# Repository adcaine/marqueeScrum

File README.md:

marqueeScrum
============

This will display a marquee message during scrums to keep people on time

This is strictly a work in progress at this time.

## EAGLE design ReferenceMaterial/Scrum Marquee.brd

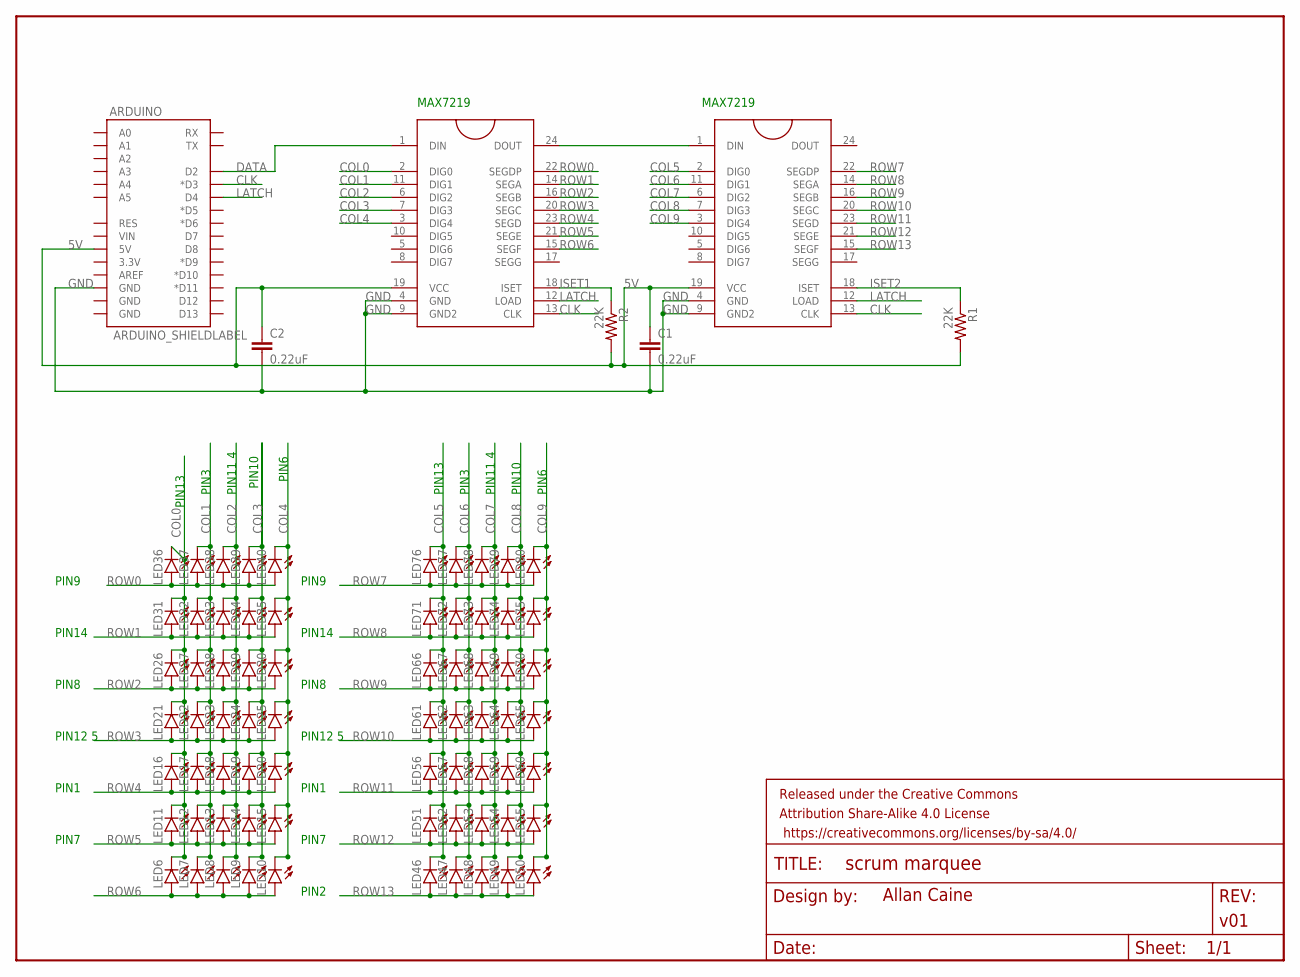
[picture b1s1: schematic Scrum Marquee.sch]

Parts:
ARDUINO: ARDUINO_SHIELDLABEL; DUEMILANOVE_SHIELD
C1, C2: 0.22uF; CAP-PTH-SMALL-KIT
FRAME1: FRAME-LETTER; CREATIVE_COMMONS
LED6, LED7, LED8, LED9, LED10, LED11, LED12, LED13, LED14, LED15, LED16, LED17, LED18, LED19, LED20, LED21, LED22, LED23, LED24, LED25, LED26, LED27, LED28, LED29, LED30, LED31, LED32, LED33, LED34, LED35, LED36, LED37, LED38, LED39, LED40, LED46, LED47, LED48, LED49, LED50, LED51, LED52, LED53, LED54, LED55, LED56, LED57, LED58, LED59, LED60, LED61, LED62, LED63, LED64, LED65, LED66, LED67, LED68, LED69, LED70, LED71, LED72, LED73, LED74, LED75, LED76, LED77, LED78, LED79, LED80: LED5MM
MAX7219DIP: MAX7219DIP; DIL24
R1, R2: 22K; AXIAL-0.4
U$2: MAX7219DIP; DIL24

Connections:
5V: ARDUINO.5V, C1.1, C2.1, MAX7219DIP.19 (VCC), R1.P$2 (2), R2.P$2 (2), U$2.19 (VCC)
CLK: ARDUINO.D3 (*D3), MAX7219DIP.13 (CLK), U$2.13 (CLK)
COL0: LED6.K (C), LED11.K (C), LED16.K (C), LED21.K (C), LED26.K (C), LED31.K (C), LED36.K (C), MAX7219DIP.2 (DIG0)
COL1: LED7.K (C), LED12.K (C), LED17.K (C), LED22.K (C), LED27.K (C), LED32.K (C), LED37.K (C), MAX7219DIP.11 (DIG1)
COL2: LED8.K (C), LED13.K (C), LED18.K (C), LED23.K (C), LED28.K (C), LED33.K (C), LED38.K (C), MAX7219DIP.6 (DIG2)
COL3: LED9.K (C), LED14.K (C), LED19.K (C), LED24.K (C), LED29.K (C), LED34.K (C), LED39.K (C), MAX7219DIP.7 (DIG3)
COL4: LED10.K (C), LED15.K (C), LED20.K (C), LED25.K (C), LED30.K (C), LED35.K (C), LED40.K (C), MAX7219DIP.3 (DIG4)
COL5: LED46.K (C), LED51.K (C), LED56.K (C), LED61.K (C), LED66.K (C), LED71.K (C), LED76.K (C), U$2.2 (DIG0)
COL6: LED47.K (C), LED52.K (C), LED57.K (C), LED62.K (C), LED67.K (C), LED72.K (C), LED77.K (C), U$2.11 (DIG1)
COL7: LED48.K (C), LED53.K (C), LED58.K (C), LED63.K (C), LED68.K (C), LED73.K (C), LED78.K (C), U$2.6 (DIG2)
COL8: LED49.K (C), LED54.K (C), LED59.K (C), LED64.K (C), LED69.K (C), LED74.K (C), LED79.K (C), U$2.7 (DIG3)
COL9: LED50.K (C), LED55.K (C), LED60.K (C), LED65.K (C), LED70.K (C), LED75.K (C), LED80.K (C), U$2.3 (DIG4)
DATA: ARDUINO.D2, MAX7219DIP.1 (DIN)
GND: ARDUINO.GND@2 (GND), C1.2, C2.2, MAX7219DIP.4 (GND), MAX7219DIP.9 (GND2), U$2.4 (GND), U$2.9 (GND2)
ISET1: MAX7219DIP.18 (ISET), R2.P$1 (1)
ISET2: R1.P$1 (1), U$2.18 (ISET)
LATCH: ARDUINO.D4, MAX7219DIP.12 (LOAD), U$2.12 (LOAD)
unnamed: MAX7219DIP.24 (DOUT), U$2.1 (DIN)
ROW0: LED36.A, LED37.A, LED38.A, LED39.A, LED40.A, MAX7219DIP.22 (SEGDP)
ROW1: LED31.A, LED32.A, LED33.A, LED34.A, LED35.A, MAX7219DIP.14 (SEGA)
ROW2: LED26.A, LED27.A, LED28.A, LED29.A, LED30.A, MAX7219DIP.16 (SEGB)
ROW3: LED21.A, LED22.A, LED23.A, LED24.A, LED25.A, MAX7219DIP.20 (SEGC)
ROW4: LED16.A, LED17.A, LED18.A, LED19.A, LED20.A, MAX7219DIP.23 (SEGD)
ROW5: LED11.A, LED12.A, LED13.A, LED14.A, LED15.A, MAX7219DIP.21 (SEGE)
ROW6: LED6.A, LED7.A, LED8.A, LED9.A, LED10.A, MAX7219DIP.15 (SEGF)
ROW7: LED76.A, LED77.A, LED78.A, LED79.A, LED80.A, U$2.22 (SEGDP)
ROW8: LED71.A, LED72.A, LED73.A, LED74.A, LED75.A, U$2.14 (SEGA)
ROW9: LED66.A, LED67.A, LED68.A, LED69.A, LED70.A, U$2.16 (SEGB)
ROW10: LED61.A, LED62.A, LED63.A, LED64.A, LED65.A, U$2.20 (SEGC)
ROW11: LED56.A, LED57.A, LED58.A, LED59.A, LED60.A, U$2.23 (SEGD)
ROW12: LED51.A, LED52.A, LED53.A, LED54.A, LED55.A, U$2.21 (SEGE)
ROW13: LED46.A, LED47.A, LED48.A, LED49.A, LED50.A, U$2.15 (SEGF)

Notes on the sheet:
MAX7219
PIN9
PIN14
PIN8
PIN12 5
PIN1
PIN7
PIN2
PIN13
PIN3
PIN11 4
PIN10
PIN6

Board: 2 copper layers, 78 parts (0 on the bottom side), 32 nets, no tracks yet.

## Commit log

2014-12-23 Initial Commit of Control Lines
2014-12-23 Added setControlLines function
2014-12-23 Correct bug in function prototype
2014-12-23 Simplified setControlLines function; still requires checking
2014-12-23 Add reference material and re-organize folders.
2014-12-23 Added Solder Time clock schematic info
2014-12-23 Corrected bug in modulus operation; set to 5 columns for 5x7 led matrix
2014-12-24 Update with corrections
2014-12-24 Adding additional reference material
2014-12-24 Added the code necessary for the shift register to function
2014-12-25 Add the showLetter function; minor corrections to shift register lines
2014-12-25 Changed code to accommodate the showing of a single letter
2014-12-31 Near final Maxim code + eagle schematics

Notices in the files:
parts and their libraries:
SparkFun-Boards: Licensing: Creative Commons ShareAlike 4.0 International - https://creativecommons.org/licenses/by-sa/4.0
SparkFun-Aesthetics: Released under the Creative Commons Attribution Share-Alike 4.0 License
SparkFun-Aesthetics: https://creativecommons.org/licenses/by-sa/4.0
